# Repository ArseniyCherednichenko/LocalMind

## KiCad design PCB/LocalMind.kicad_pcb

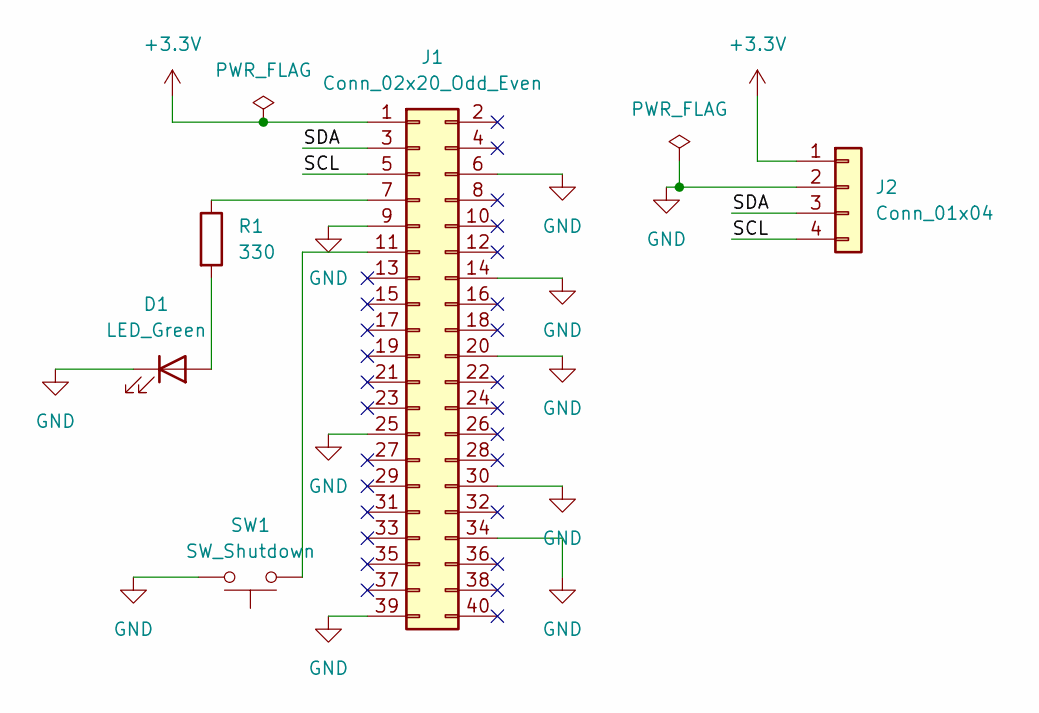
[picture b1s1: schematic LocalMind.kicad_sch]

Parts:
D1: LED_Green; LED_D5.0mm
J1: Conn_02x20_Odd_Even; PinHeader_2x20_P2.54mm_Vertical
J2: Conn_01x04; PinHeader_1x04_P2.54mm_Vertical
R1: 330; R_Axial_DIN0207_L6.3mm_D2.5mm_P10.16mm_Horizontal
SW1: SW_Shutdown; SW_PUSH_6mm

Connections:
+3.3V: J1.1, J2.1
/SCL: J1.5, J2.4
/SDA: J1.3, J2.3
GND: D1.1 (K), J1.6, J1.9, J1.14, J1.20, J1.25, J1.30, J1.34, J1.39, J2.2, SW1.2
unnamed: D1.2 (A), R1.2
unnamed: J1.7, R1.1
unnamed: J1.11, SW1.1

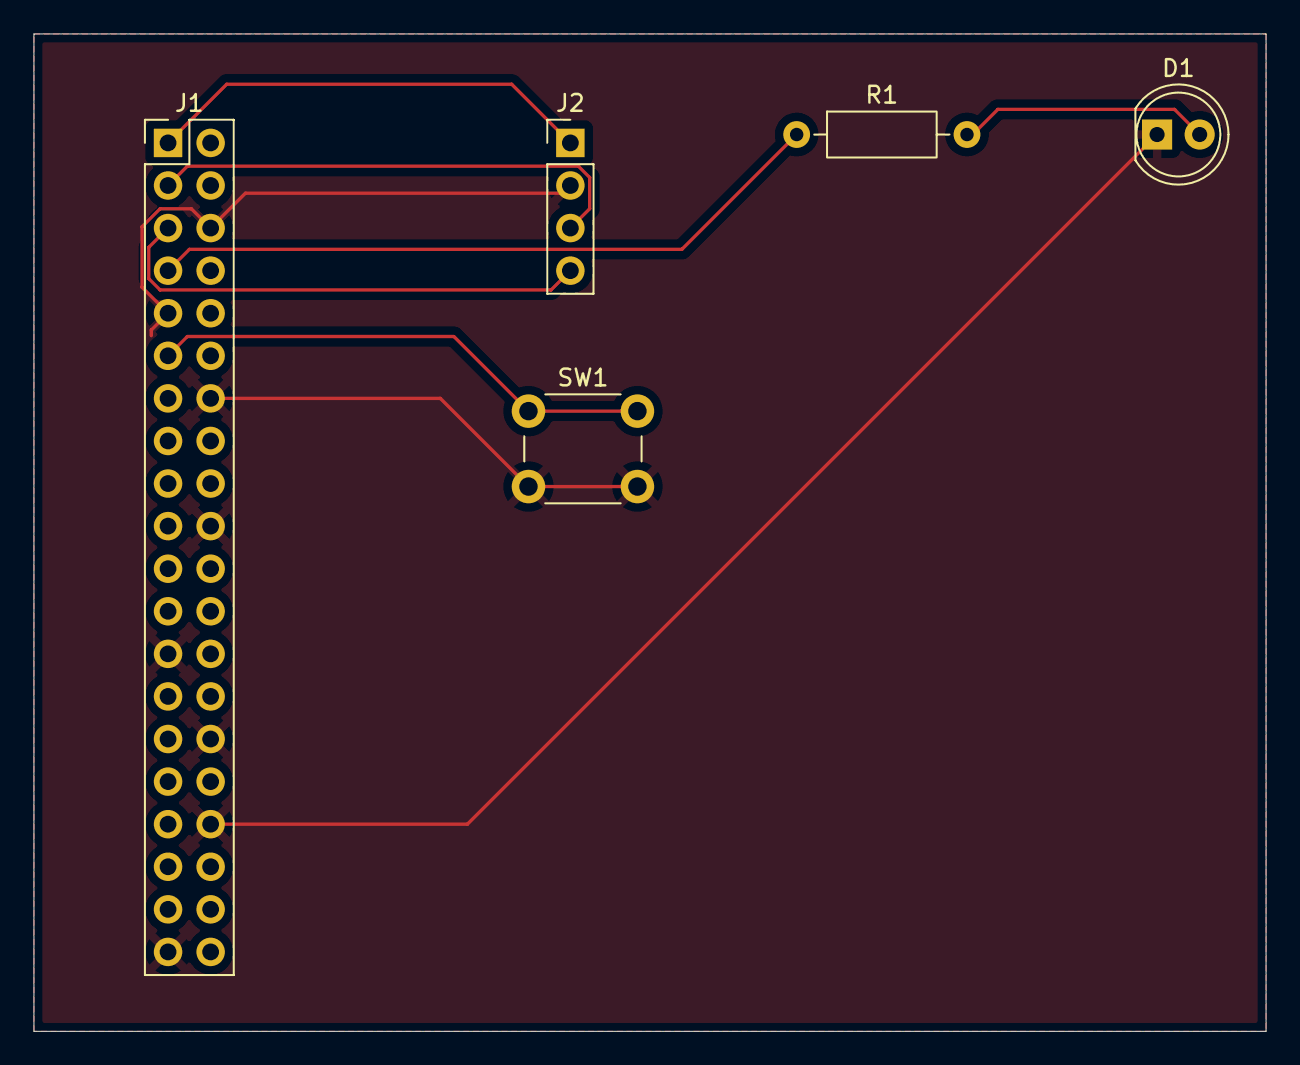
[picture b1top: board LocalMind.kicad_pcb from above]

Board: 2 copper layers, 73.5 x 59.5 mm, 5 parts (0 on the bottom side), 7 nets.

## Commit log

2026-03-10 Create pcb
2026-03-10 Create CAD
2026-03-10 Create n
2026-03-14 Add display functionality for system metrics
